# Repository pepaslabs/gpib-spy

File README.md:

# gpib-spy
A GPIB pass-through board with connectors for logic analyzers.

# Status

This board is untested (waiting for boards to arrive).

# Board design v1

Initial board design.

## Gerbers

[gerbers.zip](kicad/releases/v1/gerbers.zip)

## Schematic

[PDF](kicad/releases/v1/gpib-spy-schematic.pdf).

## Parts

* P1: Male GPIB connector
  * Norcomp Inc. 112-024-113R001
  * [$5.00 at digikey](https://www.digikey.com/product-detail/en/norcomp-inc/112-024-113R001/1024RMA-ND/955155)

* P2, P3: IDC box header, 5x2, 0.1"
  * [$0.48 at digikey](https://www.digikey.com/product-detail/en/cnc-tech/3020-10-0100-00/1175-1609-ND/3441723)
  * [$0.14 at tayda](https://www.taydaelectronics.com/connectors-sockets/box-header-connectors/10-pin-box-header-connector-2-54mm.html)
  * or search ebay for ["idc 2x5 box header"](https://www.ebay.com/sch/i.html?_nkw=idc+2x5+box+header)

* P4: Female GPIB connector
  * Norcomp Inc. 112-024-213R001
  * [$5.15 at digikey](https://www.digikey.com/product-detail/en/norcomp-inc/112-024-213R001/1024RFA-ND/955159)

# License

This board design is [Open-Source Hardware](http://www.oshwa.org/definition/).  It is licensed under the [MIT License](http://opensource.org/licenses/MIT).  It was designed by Jason Pepas.

# Thanks

Thanks to [Steven Casagrande](http://steven.casagrande.io/) of [Galvant Industries](https://github.com/Galvant) for [releasing](https://github.com/Galvant/gpibusb-pcb) his [GPIB-to-USB adapter](http://www.galvant.ca/) as open source hardware.  Using a few of his KiCAD footprints saved me a lot of time!

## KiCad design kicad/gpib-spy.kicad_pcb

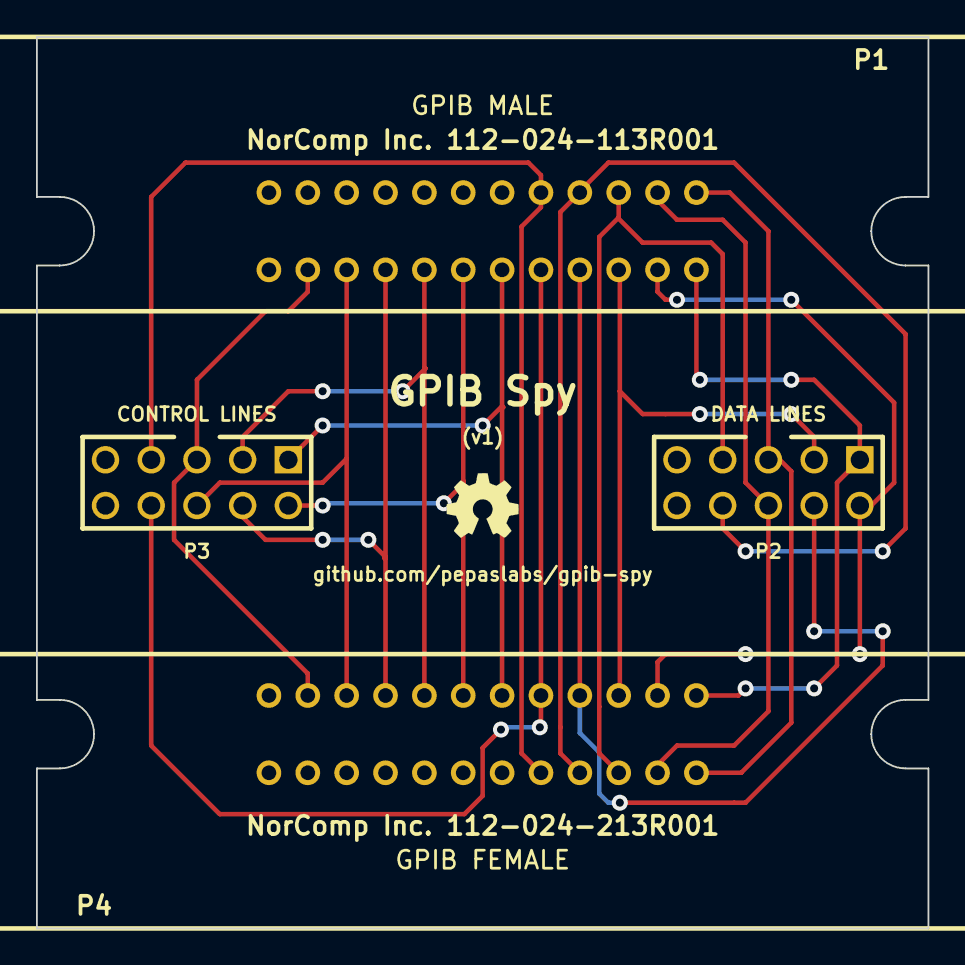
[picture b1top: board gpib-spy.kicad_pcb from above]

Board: 2 copper layers, 49.5 x 49.5 mm, 4 parts (0 on the bottom side), 17 nets.

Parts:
P1: GPIB MALE; 112-024-113R001
P2: DATA LINES; IDC_5x2
P3: CONTROL LINES; IDC_5x2
P4: GPIB FEMALE; 112-024-213R001

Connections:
GND: P1.12, P1.18, P1.19, P1.20, P1.21, P1.22, P1.23, P1.24, P2.9, P2.10, P3.9, P3.10, P4.12, P4.18, P4.19, P4.20, P4.21, P4.22, P4.23, P4.24
unnamed: P1.1, P2.1, P4.1
unnamed: P1.11, P3.5, P4.11
unnamed: P1.2, P2.2, P4.2
unnamed: P1.3, P2.3, P4.3
unnamed: P1.4, P2.4, P4.4
unnamed: P1.5, P3.8, P4.5
unnamed: P1.6, P3.1, P4.6
unnamed: P1.7, P3.2, P4.7
unnamed: P1.8, P3.3, P4.8
unnamed: P1.9, P3.4, P4.9
unnamed: P1.10, P3.6, P4.10
unnamed: P1.13, P2.5, P4.13
unnamed: P1.14, P2.6, P4.14
unnamed: P1.15, P2.7, P4.15
unnamed: P1.16, P2.8, P4.16
unnamed: P1.17, P3.7, P4.17

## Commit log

2017-07-07 Initial release
2017-07-07 adding .gitignore
2017-08-26 adding srzip scripts
